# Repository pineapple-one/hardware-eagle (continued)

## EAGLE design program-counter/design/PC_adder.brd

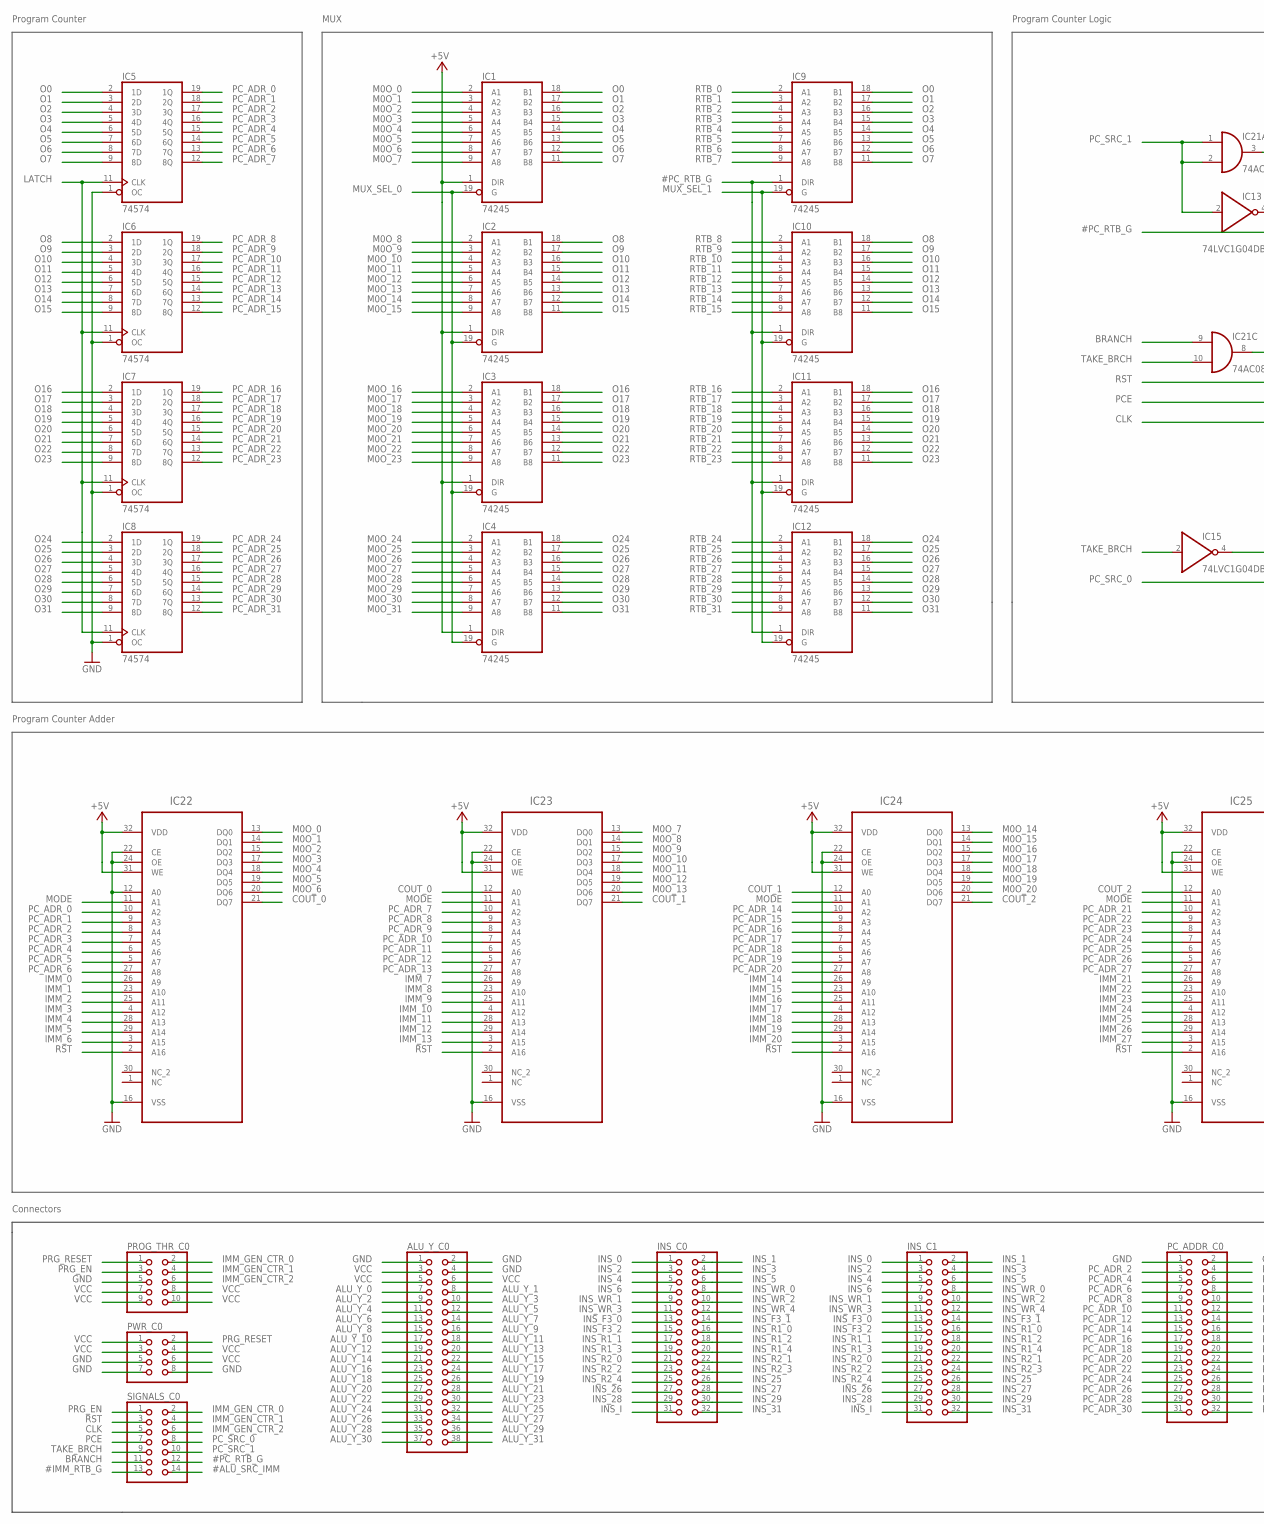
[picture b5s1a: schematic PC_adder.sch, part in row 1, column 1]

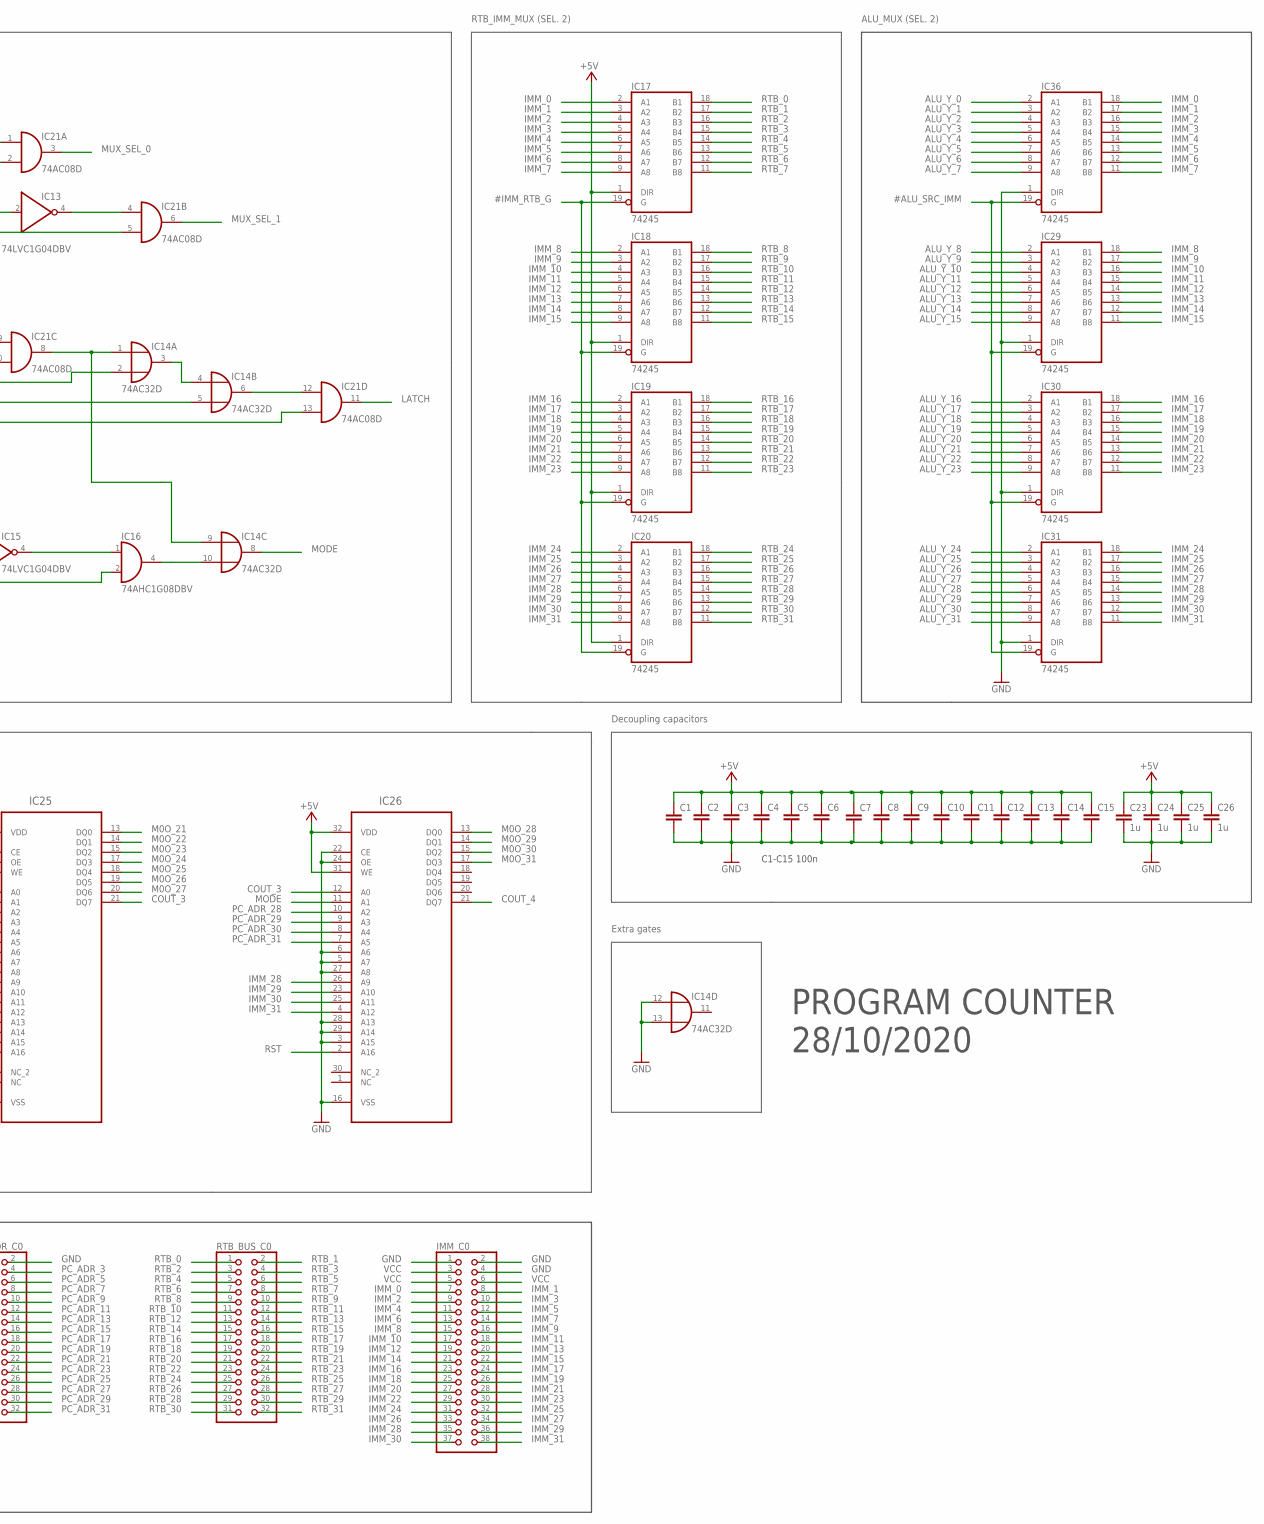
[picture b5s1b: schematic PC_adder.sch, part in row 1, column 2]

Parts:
ALU_Y_C0: PINHD-2X19; 2X19
C1, C2, C3, C4, C5, C6, C7, C8, C9, C10, C11, C12, C13, C14, C15: C-EUC0805; C0805
C23, C24, C25, C26: 1u; C0805
IC1, IC2, IC3, IC4, IC9, IC10, IC11, IC12, IC17, IC18, IC19, IC20, IC29, IC30, IC31, IC36: 74245; TSSOP20
IC5, IC6, IC7, IC8: 74574; TSSOP20
IC13, IC15: 74LVC1G04DBV; SOT23-5
IC14: 74AC32D; SO14
IC16: 74AHC1G08DBV; SOT23-5
IC21: 74AC08D; SO14
IC22, IC23, IC24, IC25, IC26: SST39SF010A-70-4I-NHEPLCC32; S32
IMM_C0: PINHD-2X19; 2X19
INS_C0, INS_C1: PINHD-2X16; 2X16
PC_ADDR_C0: PINHD-2X16; 2X16
PROG_THR_C0: PINHD-2X5; 2X05
PWR_C0: PINHD-2X4; 2X04
RTB_BUS_C0: PINHD-2X16; 2X16
SIGNALS_C0: PINHD-2X7; 2X07

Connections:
#ALU_SRC_IMM: IC29.19 (G), IC30.19 (G), IC31.19 (G), IC36.19 (G), SIGNALS_C0.14
#IMM_RTB_G: IC17.19 (G), IC18.19 (G), IC19.19 (G), IC20.19 (G), SIGNALS_C0.13
#PC_RTB_G: IC9.1 (DIR), IC10.1 (DIR), IC11.1 (DIR), IC12.1 (DIR), IC21.5 (I1), SIGNALS_C0.12
ALU_Y_0: ALU_Y_C0.7, IC36.2 (A1)
ALU_Y_1: ALU_Y_C0.8, IC36.3 (A2)
ALU_Y_2: ALU_Y_C0.9, IC36.4 (A3)
ALU_Y_3: ALU_Y_C0.10, IC36.5 (A4)
ALU_Y_4: ALU_Y_C0.11, IC36.6 (A5)
ALU_Y_5: ALU_Y_C0.12, IC36.7 (A6)
ALU_Y_6: ALU_Y_C0.13, IC36.8 (A7)
ALU_Y_7: ALU_Y_C0.14, IC36.9 (A8)
ALU_Y_8: ALU_Y_C0.15, IC29.2 (A1)
ALU_Y_9: ALU_Y_C0.16, IC29.3 (A2)
ALU_Y_10: ALU_Y_C0.17, IC29.4 (A3)
ALU_Y_11: ALU_Y_C0.18, IC29.5 (A4)
ALU_Y_12: ALU_Y_C0.19, IC29.6 (A5)
ALU_Y_13: ALU_Y_C0.20, IC29.7 (A6)
ALU_Y_14: ALU_Y_C0.21, IC29.8 (A7)
ALU_Y_15: ALU_Y_C0.22, IC29.9 (A8)
ALU_Y_16: ALU_Y_C0.23, IC30.2 (A1)
ALU_Y_17: ALU_Y_C0.24, IC30.3 (A2)
ALU_Y_18: ALU_Y_C0.25, IC30.4 (A3)
ALU_Y_19: ALU_Y_C0.26, IC30.5 (A4)
ALU_Y_20: ALU_Y_C0.27, IC30.6 (A5)
ALU_Y_21: ALU_Y_C0.28, IC30.7 (A6)
ALU_Y_22: ALU_Y_C0.29, IC30.8 (A7)
ALU_Y_23: ALU_Y_C0.30, IC30.9 (A8)
ALU_Y_24: ALU_Y_C0.31, IC31.2 (A1)
ALU_Y_25: ALU_Y_C0.32, IC31.3 (A2)
ALU_Y_26: ALU_Y_C0.33, IC31.4 (A3)
ALU_Y_27: ALU_Y_C0.34, IC31.5 (A4)
ALU_Y_28: ALU_Y_C0.35, IC31.6 (A5)
ALU_Y_29: ALU_Y_C0.36, IC31.7 (A6)
ALU_Y_30: ALU_Y_C0.37, IC31.8 (A7)
ALU_Y_31: ALU_Y_C0.38, IC31.9 (A8)
BRANCH: IC21.9 (I0), SIGNALS_C0.11
BRANCH1: IC14.6 (O), IC21.12 (I0)
BRANCH2: IC15.4 (O), IC16.1 (I0)
BRCH&PC: IC14.10 (I1), IC16.4 (O)
CLK: IC21.13 (I1), SIGNALS_C0.5
COUT_0: IC22.21 (DQ7), IC23.12 (A0)
COUT_1: IC23.21 (DQ7), IC24.12 (A0)
COUT_2: IC24.21 (DQ7), IC25.12 (A0)
COUT_3: IC25.21 (DQ7), IC26.12 (A0)
COUT_4: IC26.21 (DQ7)
GND: ALU_Y_C0.1, ALU_Y_C0.2, ALU_Y_C0.4, C1.2, C2.2, C3.2, C4.2, C5.2, C6.2, C7.2, C8.2, C9.2, C10.2, C11.2, C12.2, C13.2, C14.2, C15.2, C23.2, C24.2, C25.2, C26.2, IC1.10 (GND), IC2.10 (GND), IC3.10 (GND), IC4.10 (GND), IC5.1 (OC), IC5.10 (GND), IC6.1 (OC), IC6.10 (GND), IC7.1 (OC), IC7.10 (GND), IC8.1 (OC), IC8.10 (GND), IC9.10 (GND), IC10.10 (GND), IC11.10 (GND), IC12.10 (GND), IC13.3 (GND), IC14.7 (GND), IC14.12 (I0), IC14.13 (I1), IC15.3 (GND), IC16.3 (GND), IC17.10 (GND), IC18.10 (GND), IC19.10 (GND), IC20.10 (GND), IC21.7 (GND), IC22.12 (A0), IC22.16 (VSS), IC22.22 (CE), IC22.24 (OE), IC23.16 (VSS), IC23.22 (CE), IC23.24 (OE), IC24.16 (VSS), IC24.22 (CE), IC24.24 (OE), IC25.16 (VSS), IC25.22 (CE), IC25.24 (OE), IC26.3 (A15), IC26.5 (A7), IC26.6 (A6), IC26.16 (VSS), IC26.22 (CE), IC26.24 (OE), IC26.27 (A8), IC26.28 (A13), IC26.29 (A14), IC29.1 (DIR), IC29.10 (GND), IC30.1 (DIR), IC30.10 (GND), IC31.1 (DIR), IC31.10 (GND), IC36.1 (DIR), IC36.10 (GND), IMM_C0.1, IMM_C0.2, IMM_C0.4, PC_ADDR_C0.1, PC_ADDR_C0.2, PROG_THR_C0.5, PWR_C0.5, PWR_C0.7, PWR_C0.8
IMM_0: IC17.2 (A1), IC22.26 (A9), IC36.18 (B1), IMM_C0.7
IMM_1: IC17.3 (A2), IC22.23 (A10), IC36.17 (B2), IMM_C0.8
IMM_2: IC17.4 (A3), IC22.25 (A11), IC36.16 (B3), IMM_C0.9
IMM_3: IC17.5 (A4), IC22.4 (A12), IC36.15 (B4), IMM_C0.10
IMM_4: IC17.6 (A5), IC22.28 (A13), IC36.14 (B5), IMM_C0.11
IMM_5: IC17.7 (A6), IC22.29 (A14), IC36.13 (B6), IMM_C0.12
IMM_6: IC17.8 (A7), IC22.3 (A15), IC36.12 (B7), IMM_C0.13
IMM_7: IC17.9 (A8), IC23.26 (A9), IC36.11 (B8), IMM_C0.14
IMM_8: IC18.2 (A1), IC23.23 (A10), IC29.18 (B1), IMM_C0.15
IMM_9: IC18.3 (A2), IC23.25 (A11), IC29.17 (B2), IMM_C0.16
IMM_10: IC18.4 (A3), IC23.4 (A12), IC29.16 (B3), IMM_C0.17
IMM_11: IC18.5 (A4), IC23.28 (A13), IC29.15 (B4), IMM_C0.18
IMM_12: IC18.6 (A5), IC23.29 (A14), IC29.14 (B5), IMM_C0.19
IMM_13: IC18.7 (A6), IC23.3 (A15), IC29.13 (B6), IMM_C0.20
IMM_14: IC18.8 (A7), IC24.26 (A9), IC29.12 (B7), IMM_C0.21
IMM_15: IC18.9 (A8), IC24.23 (A10), IC29.11 (B8), IMM_C0.22
IMM_16: IC19.2 (A1), IC24.25 (A11), IC30.18 (B1), IMM_C0.23
IMM_17: IC19.3 (A2), IC24.4 (A12), IC30.17 (B2), IMM_C0.24
IMM_18: IC19.4 (A3), IC24.28 (A13), IC30.16 (B3), IMM_C0.25
IMM_19: IC19.5 (A4), IC24.29 (A14), IC30.15 (B4), IMM_C0.26
IMM_20: IC19.6 (A5), IC24.3 (A15), IC30.14 (B5), IMM_C0.27
IMM_21: IC19.7 (A6), IC25.26 (A9), IC30.13 (B6), IMM_C0.28
IMM_22: IC19.8 (A7), IC25.23 (A10), IC30.12 (B7), IMM_C0.29
IMM_23: IC19.9 (A8), IC25.25 (A11), IC30.11 (B8), IMM_C0.30
IMM_24: IC20.2 (A1), IC25.4 (A12), IC31.18 (B1), IMM_C0.31
IMM_25: IC20.3 (A2), IC25.28 (A13), IC31.17 (B2), IMM_C0.32
IMM_26: IC20.4 (A3), IC25.29 (A14), IC31.16 (B3), IMM_C0.33
IMM_27: IC20.5 (A4), IC25.3 (A15), IC31.15 (B4), IMM_C0.34
IMM_28: IC20.6 (A5), IC26.26 (A9), IC31.14 (B5), IMM_C0.35
IMM_29: IC20.7 (A6), IC26.23 (A10), IC31.13 (B6), IMM_C0.36
IMM_30: IC20.8 (A7), IC26.25 (A11), IC31.12 (B7), IMM_C0.37
IMM_31: IC20.9 (A8), IC26.4 (A12), IC31.11 (B8), IMM_C0.38
IMM_GEN_CTR_0: PROG_THR_C0.2, SIGNALS_C0.2
IMM_GEN_CTR_1: PROG_THR_C0.4, SIGNALS_C0.4
IMM_GEN_CTR_2: PROG_THR_C0.6, SIGNALS_C0.6
INS_0: INS_C0.1, INS_C1.1
INS_1: INS_C0.2, INS_C1.2
INS_2: INS_C0.3, INS_C1.3
INS_3: INS_C0.4, INS_C1.4
INS_4: INS_C0.5, INS_C1.5
INS_5: INS_C0.6, INS_C1.6
INS_6: INS_C0.7, INS_C1.7
INS_25: INS_C0.26, INS_C1.26
INS_26: INS_C0.27, INS_C1.27
INS_27: INS_C0.28, INS_C1.28
INS_28: INS_C0.29, INS_C1.29
INS_29: INS_C0.30, INS_C1.30
INS_31: INS_C0.32, INS_C1.32
INS_F3_0: INS_C0.13, INS_C1.13
INS_F3_1: INS_C0.14, INS_C1.14
INS_F3_2: INS_C0.15, INS_C1.15
INS_I: INS_C0.31, INS_C1.31
INS_R1_0: INS_C0.16, INS_C1.16
INS_R1_1: INS_C0.17, INS_C1.17
INS_R1_2: INS_C0.18, INS_C1.18
INS_R1_3: INS_C0.19, INS_C1.19
INS_R1_4: INS_C0.20, INS_C1.20
INS_R2_0: INS_C0.21, INS_C1.21
INS_R2_1: INS_C0.22, INS_C1.22
INS_R2_2: INS_C0.23, INS_C1.23
INS_R2_3: INS_C0.24, INS_C1.24
INS_R2_4: INS_C0.25, INS_C1.25
INS_WR_0: INS_C0.8, INS_C1.8
INS_WR_1: INS_C0.9, INS_C1.9
INS_WR_2: INS_C0.10, INS_C1.10
INS_WR_3: INS_C0.11, INS_C1.11
INS_WR_4: INS_C0.12, INS_C1.12
LATCH: IC5.11 (CLK), IC6.11 (CLK), IC7.11 (CLK), IC8.11 (CLK), IC21.11 (O)
M0O_0: IC1.2 (A1), IC22.13 (DQ0)
M0O_1: IC1.3 (A2), IC22.14 (DQ1)
M0O_2: IC1.4 (A3), IC22.15 (DQ2)
M0O_3: IC1.5 (A4), IC22.17 (DQ3)
M0O_4: IC1.6 (A5), IC22.18 (DQ4)
M0O_5: IC1.7 (A6), IC22.19 (DQ5)
M0O_6: IC1.8 (A7), IC22.20 (DQ6)
M0O_7: IC1.9 (A8), IC23.13 (DQ0)
M0O_8: IC2.2 (A1), IC23.14 (DQ1)
M0O_9: IC2.3 (A2), IC23.15 (DQ2)
M0O_10: IC2.4 (A3), IC23.17 (DQ3)
M0O_11: IC2.5 (A4), IC23.18 (DQ4)
M0O_12: IC2.6 (A5), IC23.19 (DQ5)
M0O_13: IC2.7 (A6), IC23.20 (DQ6)
M0O_14: IC2.8 (A7), IC24.13 (DQ0)
M0O_15: IC2.9 (A8), IC24.14 (DQ1)
M0O_16: IC3.2 (A1), IC24.15 (DQ2)
M0O_17: IC3.3 (A2), IC24.17 (DQ3)
M0O_18: IC3.4 (A3), IC24.18 (DQ4)
M0O_19: IC3.5 (A4), IC24.19 (DQ5)
M0O_20: IC3.6 (A5), IC24.20 (DQ6)
M0O_21: IC3.7 (A6), IC25.13 (DQ0)
M0O_22: IC3.8 (A7), IC25.14 (DQ1)
M0O_23: IC3.9 (A8), IC25.15 (DQ2)
M0O_24: IC4.2 (A1), IC25.17 (DQ3)
M0O_25: IC4.3 (A2), IC25.18 (DQ4)
M0O_26: IC4.4 (A3), IC25.19 (DQ5)
M0O_27: IC4.5 (A4), IC25.20 (DQ6)
M0O_28: IC4.6 (A5), IC26.13 (DQ0)
M0O_29: IC4.7 (A6), IC26.14 (DQ1)
M0O_30: IC4.8 (A7), IC26.15 (DQ2)
M0O_31: IC4.9 (A8), IC26.17 (DQ3)
MODE: IC14.8 (O), IC22.11 (A1), IC23.11 (A1), IC24.11 (A1), IC25.11 (A1), IC26.11 (A1)
MUX_SEL_0: IC1.19 (G), IC2.19 (G), IC3.19 (G), IC4.19 (G), IC21.3 (O)
MUX_SEL_1: IC9.19 (G), IC10.19 (G), IC11.19 (G), IC12.19 (G), IC21.6 (O)
unnamed: IC13.4 (O), IC21.4 (I0)
unnamed: IC14.1 (I0), IC14.9 (I0), IC21.8 (O)
unnamed: IC14.3 (O), IC14.4 (I0)
O0: IC1.18 (B1), IC5.2 (1D), IC9.18 (B1)
O1: IC1.17 (B2), IC5.3 (2D), IC9.17 (B2)
O2: IC1.16 (B3), IC5.4 (3D), IC9.16 (B3)
O3: IC1.15 (B4), IC5.5 (4D), IC9.15 (B4)
O4: IC1.14 (B5), IC5.6 (5D), IC9.14 (B5)
O5: IC1.13 (B6), IC5.7 (6D), IC9.13 (B6)
O6: IC1.12 (B7), IC5.8 (7D), IC9.12 (B7)
O7: IC1.11 (B8), IC5.9 (8D), IC9.11 (B8)
O8: IC2.18 (B1), IC6.2 (1D), IC10.18 (B1)
O9: IC2.17 (B2), IC6.3 (2D), IC10.17 (B2)
O10: IC2.16 (B3), IC6.4 (3D), IC10.16 (B3)
O11: IC2.15 (B4), IC6.5 (4D), IC10.15 (B4)
O12: IC2.14 (B5), IC6.6 (5D), IC10.14 (B5)
O13: IC2.13 (B6), IC6.7 (6D), IC10.13 (B6)
O14: IC2.12 (B7), IC6.8 (7D), IC10.12 (B7)
O15: IC2.11 (B8), IC6.9 (8D), IC10.11 (B8)
O16: IC3.18 (B1), IC7.2 (1D), IC11.18 (B1)
O17: IC3.17 (B2), IC7.3 (2D), IC11.17 (B2)
O18: IC3.16 (B3), IC7.4 (3D), IC11.16 (B3)
O19: IC3.15 (B4), IC7.5 (4D), IC11.15 (B4)
O20: IC3.14 (B5), IC7.6 (5D), IC11.14 (B5)
O21: IC3.13 (B6), IC7.7 (6D), IC11.13 (B6)
O22: IC3.12 (B7), IC7.8 (7D), IC11.12 (B7)
O23: IC3.11 (B8), IC7.9 (8D), IC11.11 (B8)
O24: IC4.18 (B1), IC8.2 (1D), IC12.18 (B1)
O25: IC4.17 (B2), IC8.3 (2D), IC12.17 (B2)
O26: IC4.16 (B3), IC8.4 (3D), IC12.16 (B3)
O27: IC4.15 (B4), IC8.5 (4D), IC12.15 (B4)
O28: IC4.14 (B5), IC8.6 (5D), IC12.14 (B5)
O29: IC4.13 (B6), IC8.7 (6D), IC12.13 (B6)
O30: IC4.12 (B7), IC8.8 (7D), IC12.12 (B7)
O31: IC4.11 (B8), IC8.9 (8D), IC12.11 (B8)
PCE: IC14.5 (I1), SIGNALS_C0.7
PC_ADR_0: IC5.19 (1Q), IC22.10 (A2)
PC_ADR_1: IC5.18 (2Q), IC22.9 (A3)
PC_ADR_2: IC5.17 (3Q), IC22.8 (A4), PC_ADDR_C0.3
PC_ADR_3: IC5.16 (4Q), IC22.7 (A5), PC_ADDR_C0.4
PC_ADR_4: IC5.15 (5Q), IC22.6 (A6), PC_ADDR_C0.5
PC_ADR_5: IC5.14 (6Q), IC22.5 (A7), PC_ADDR_C0.6
PC_ADR_6: IC5.13 (7Q), IC22.27 (A8), PC_ADDR_C0.7
PC_ADR_7: IC5.12 (8Q), IC23.10 (A2), PC_ADDR_C0.8
PC_ADR_8: IC6.19 (1Q), IC23.9 (A3), PC_ADDR_C0.9
PC_ADR_9: IC6.18 (2Q), IC23.8 (A4), PC_ADDR_C0.10
PC_ADR_10: IC6.17 (3Q), IC23.7 (A5), PC_ADDR_C0.11
PC_ADR_11: IC6.16 (4Q), IC23.6 (A6), PC_ADDR_C0.12
PC_ADR_12: IC6.15 (5Q), IC23.5 (A7), PC_ADDR_C0.13
PC_ADR_13: IC6.14 (6Q), IC23.27 (A8), PC_ADDR_C0.14
PC_ADR_14: IC6.13 (7Q), IC24.10 (A2), PC_ADDR_C0.15
PC_ADR_15: IC6.12 (8Q), IC24.9 (A3), PC_ADDR_C0.16
PC_ADR_16: IC7.19 (1Q), IC24.8 (A4), PC_ADDR_C0.17
PC_ADR_17: IC7.18 (2Q), IC24.7 (A5), PC_ADDR_C0.18
PC_ADR_18: IC7.17 (3Q), IC24.6 (A6), PC_ADDR_C0.19
PC_ADR_19: IC7.16 (4Q), IC24.5 (A7), PC_ADDR_C0.20
PC_ADR_20: IC7.15 (5Q), IC24.27 (A8), PC_ADDR_C0.21
PC_ADR_21: IC7.14 (6Q), IC25.10 (A2), PC_ADDR_C0.22
PC_ADR_22: IC7.13 (7Q), IC25.9 (A3), PC_ADDR_C0.23
PC_ADR_23: IC7.12 (8Q), IC25.8 (A4), PC_ADDR_C0.24
PC_ADR_24: IC8.19 (1Q), IC25.7 (A5), PC_ADDR_C0.25
PC_ADR_25: IC8.18 (2Q), IC25.6 (A6), PC_ADDR_C0.26
PC_ADR_26: IC8.17 (3Q), IC25.5 (A7), PC_ADDR_C0.27
PC_ADR_27: IC8.16 (4Q), IC25.27 (A8), PC_ADDR_C0.28
PC_ADR_28: IC8.15 (5Q), IC26.10 (A2), PC_ADDR_C0.29
PC_ADR_29: IC8.14 (6Q), IC26.9 (A3), PC_ADDR_C0.30
PC_ADR_30: IC8.13 (7Q), IC26.8 (A4), PC_ADDR_C0.31
PC_ADR_31: IC8.12 (8Q), IC26.7 (A5), PC_ADDR_C0.32
PC_SRC_0: IC16.2 (I1), SIGNALS_C0.8
PC_SRC_1: IC13.2 (I), IC21.1 (I0), IC21.2 (I1), SIGNALS_C0.10
PRG_EN: PROG_THR_C0.3, SIGNALS_C0.1
PRG_RESET: PROG_THR_C0.1, PWR_C0.2
RST: IC14.2 (I1), IC22.2 (A16), IC23.2 (A16), IC24.2 (A16), IC25.2 (A16), IC26.2 (A16), SIGNALS_C0.3
RTB_0: IC9.2 (A1), IC17.18 (B1), RTB_BUS_C0.1
RTB_1: IC9.3 (A2), IC17.17 (B2), RTB_BUS_C0.2
RTB_2: IC9.4 (A3), IC17.16 (B3), RTB_BUS_C0.3
RTB_3: IC9.5 (A4), IC17.15 (B4), RTB_BUS_C0.4
RTB_4: IC9.6 (A5), IC17.14 (B5), RTB_BUS_C0.5
RTB_5: IC9.7 (A6), IC17.13 (B6), RTB_BUS_C0.6
RTB_6: IC9.8 (A7), IC17.12 (B7), RTB_BUS_C0.7
RTB_7: IC9.9 (A8), IC17.11 (B8), RTB_BUS_C0.8
RTB_8: IC10.2 (A1), IC18.18 (B1), RTB_BUS_C0.9
RTB_9: IC10.3 (A2), IC18.17 (B2), RTB_BUS_C0.10
RTB_10: IC10.4 (A3), IC18.16 (B3), RTB_BUS_C0.11
RTB_11: IC10.5 (A4), IC18.15 (B4), RTB_BUS_C0.12
RTB_12: IC10.6 (A5), IC18.14 (B5), RTB_BUS_C0.13
RTB_13: IC10.7 (A6), IC18.13 (B6), RTB_BUS_C0.14
RTB_14: IC10.8 (A7), IC18.12 (B7), RTB_BUS_C0.15
RTB_15: IC10.9 (A8), IC18.11 (B8), RTB_BUS_C0.16
RTB_16: IC11.2 (A1), IC19.18 (B1), RTB_BUS_C0.17
RTB_17: IC11.3 (A2), IC19.17 (B2), RTB_BUS_C0.18
RTB_18: IC11.4 (A3), IC19.16 (B3), RTB_BUS_C0.19
RTB_19: IC11.5 (A4), IC19.15 (B4), RTB_BUS_C0.20
RTB_20: IC11.6 (A5), IC19.14 (B5), RTB_BUS_C0.21
RTB_21: IC11.7 (A6), IC19.13 (B6), RTB_BUS_C0.22
RTB_22: IC11.8 (A7), IC19.12 (B7), RTB_BUS_C0.23
RTB_23: IC11.9 (A8), IC19.11 (B8), RTB_BUS_C0.24
RTB_24: IC12.2 (A1), IC20.18 (B1), RTB_BUS_C0.25
RTB_25: IC12.3 (A2), IC20.17 (B2), RTB_BUS_C0.26
RTB_26: IC12.4 (A3), IC20.16 (B3), RTB_BUS_C0.27
RTB_27: IC12.5 (A4), IC20.15 (B4), RTB_BUS_C0.28
RTB_28: IC12.6 (A5), IC20.14 (B5), RTB_BUS_C0.29
RTB_29: IC12.7 (A6), IC20.13 (B6), RTB_BUS_C0.30
RTB_30: IC12.8 (A7), IC20.12 (B7), RTB_BUS_C0.31
RTB_31: IC12.9 (A8), IC20.11 (B8), RTB_BUS_C0.32
TAKE_BRCH: IC15.2 (I), IC21.10 (I1), SIGNALS_C0.9
VCC: ALU_Y_C0.3, ALU_Y_C0.5, ALU_Y_C0.6, C1.1, C2.1, C3.1, C4.1, C5.1, C6.1, C7.1, C8.1, C9.1, C10.1, C11.1, C12.1, C13.1, C14.1, C15.1, C23.1, C24.1, C25.1, C26.1, IC1.1 (DIR), IC1.20 (VCC), IC2.1 (DIR), IC2.20 (VCC), IC3.1 (DIR), IC3.20 (VCC), IC4.1 (DIR), IC4.20 (VCC), IC5.20 (VCC), IC6.20 (VCC), IC7.20 (VCC), IC8.20 (VCC), IC9.20 (VCC), IC10.20 (VCC), IC11.20 (VCC), IC12.20 (VCC), IC13.5 (VCC), IC14.14 (VCC), IC15.5 (VCC), IC16.5 (VCC), IC17.1 (DIR), IC17.20 (VCC), IC18.1 (DIR), IC18.20 (VCC), IC19.1 (DIR), IC19.20 (VCC), IC20.1 (DIR), IC20.20 (VCC), IC21.14 (VCC), IC22.31 (WE), IC22.32 (VDD), IC23.31 (WE), IC23.32 (VDD), IC24.31 (WE), IC24.32 (VDD), IC25.31 (WE), IC25.32 (VDD), IC26.31 (WE), IC26.32 (VDD), IC29.20 (VCC), IC30.20 (VCC), IC31.20 (VCC), IC36.20 (VCC), IMM_C0.3, IMM_C0.5, IMM_C0.6, PROG_THR_C0.7, PROG_THR_C0.8, PROG_THR_C0.9, PROG_THR_C0.10, PWR_C0.1, PWR_C0.3, PWR_C0.4, PWR_C0.6

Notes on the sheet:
Decoupling capacitors
MUX
Program Counter
Program Counter Adder
Extra gates
Program Counter Logic
RTB_IMM_MUX (SEL. 2)
ALU_MUX (SEL. 2)
Connectors
C1-C15 100n
PROGRAM COUNTER 28/10/2020

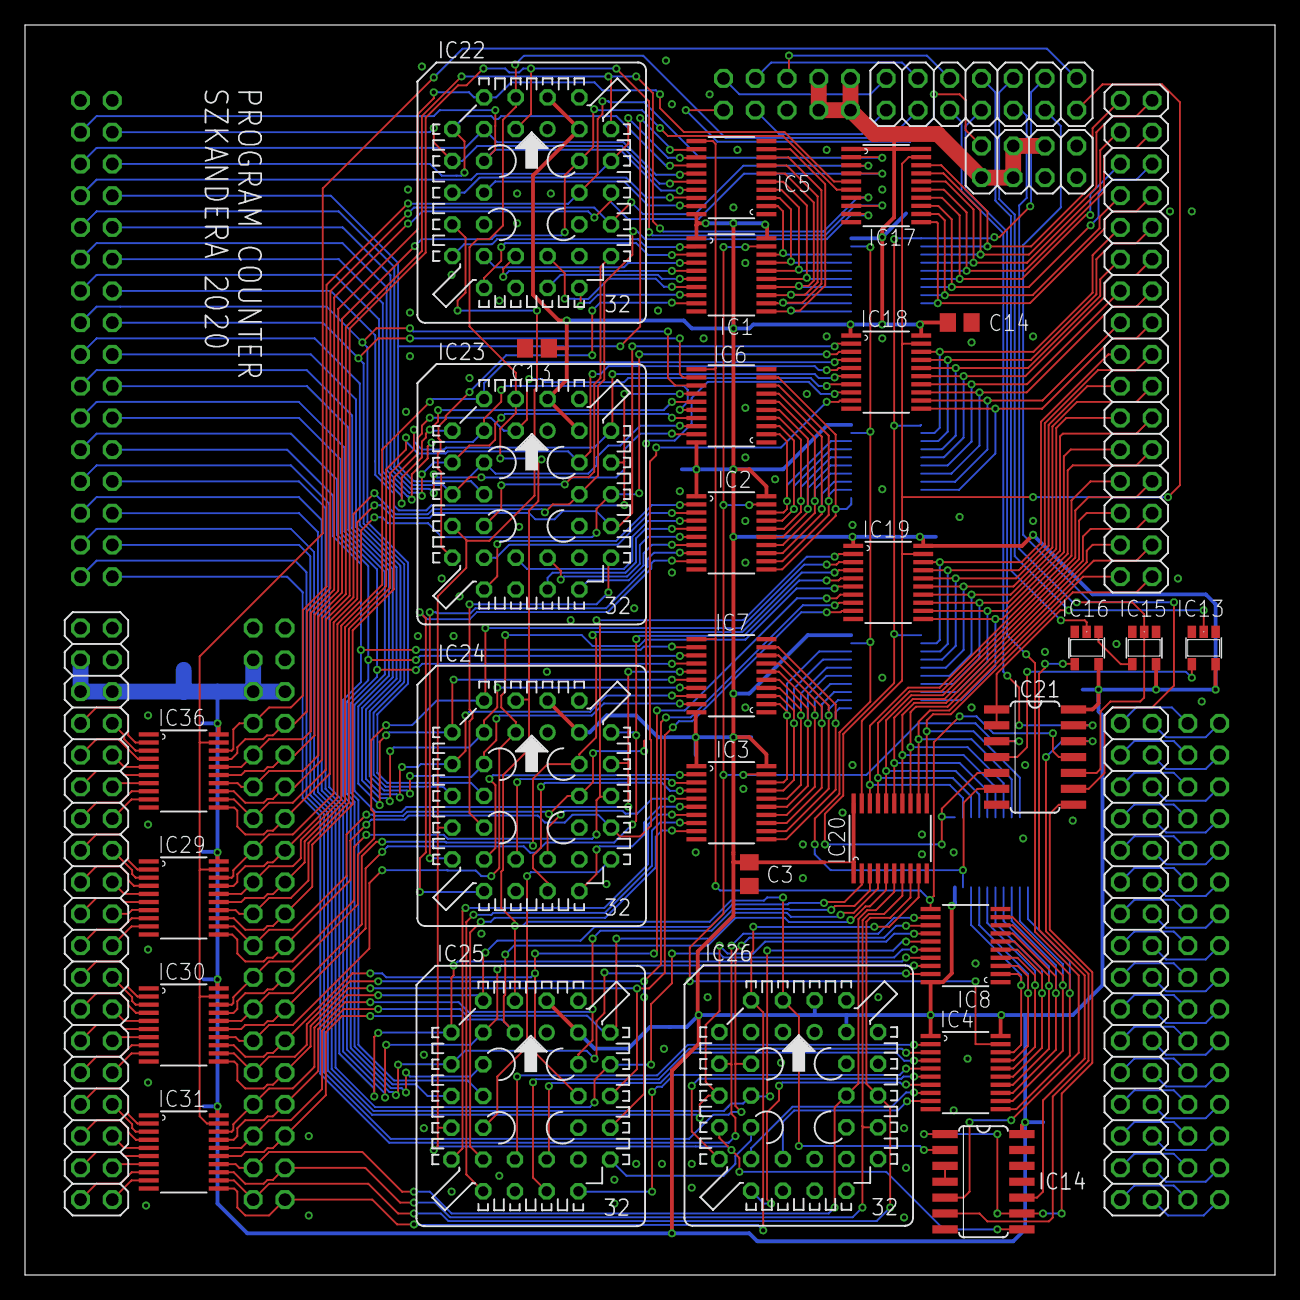
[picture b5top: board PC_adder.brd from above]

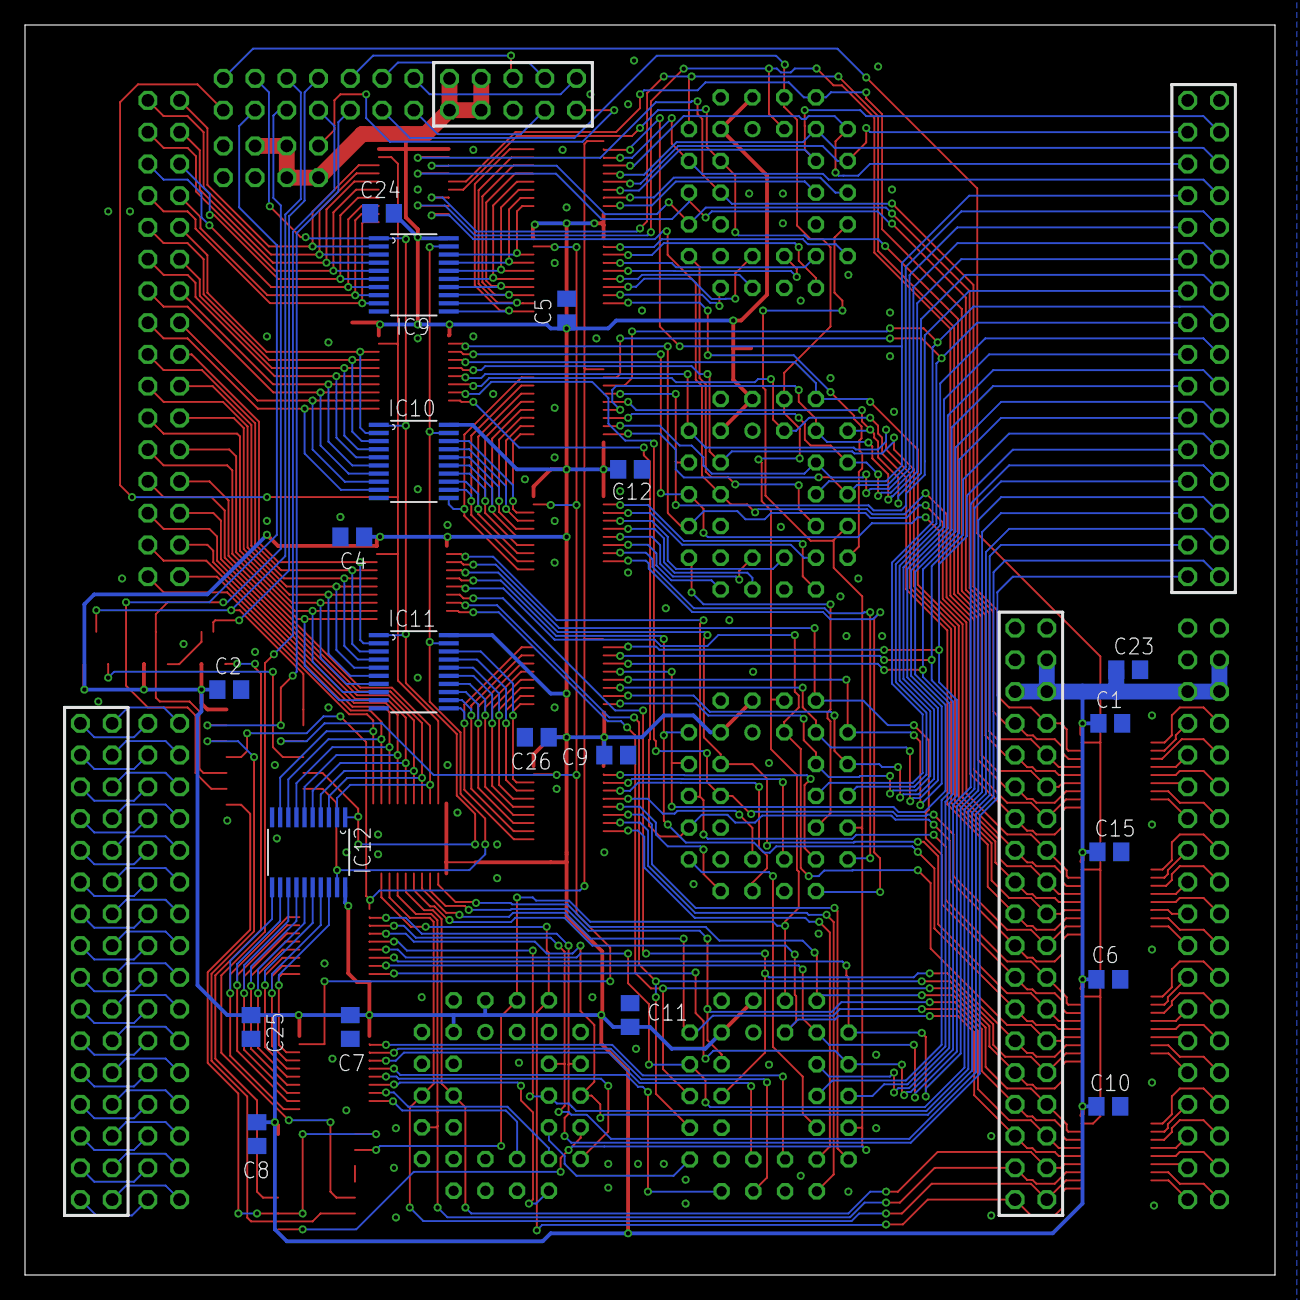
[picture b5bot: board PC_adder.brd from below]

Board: 2 copper layers, 100.0 x 100.0 mm, 58 parts (20 on the bottom side), 255 nets.
